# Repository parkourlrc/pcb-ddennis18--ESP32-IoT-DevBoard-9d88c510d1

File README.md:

# ESP32-IoT PCB

An ESP32-C3 based IoT controller board designed in KiCad. The board combines
wireless control, sensor interfaces, local storage, audio/light sensing, USB
connectivity, and single-cell Li-ion battery support on a compact four-layer
PCB.

## Main features

- **ESP32-C3-WROOM-02-H4** wireless microcontroller module
- **BME280** environmental sensor
- **MicroSD card** interface
- **W25Q32JV** external SPI flash
- **MAX4466** microphone amplifier and **CMC-5042PF-AC** microphone
- **TEMT6000X01** ambient light sensor
- **USB-C** connector with:
  - CP2102N USB-to-UART bridge
  - USB ESD protection
  - Boot and reset controls
- **Single-cell Li-ion power path**:
  - MCP73871 charger/power-path controller
  - JST battery connector
  - 3.3 V LM1117 regulator
- Status and activity LEDs
- Exposed SPI test points for SCLK, MOSI, MISO, chip select, and SD chip select
- Two M2 mounting holes

## PCB specifications

| Property | Value |
| --- | --- |
| Board thickness | 1.6 mm |
| Layer count | 4 copper layers |
| Copper stack | F.Cu / In1.Cu / In2.Cu / B.Cu |
| Copper thickness | 35 µm per copper layer |
| Core material | FR-4 |
| Approximate outline | 96.5 mm × 54.4 mm |
| Minimum routed trace width | 0.20 mm |
| Minimum routed spacing | 0.15 mm |
| Solder mask | Top and bottom |
| Silkscreen | Top and bottom |
| Finish | Not specified in the KiCad board setup; confirm with the fabricator |

The board outline includes a stepped/notched section around the USB connector
edge. Use the `Edge.Cuts` layer in the KiCad board file, rather than the
approximate dimensions above, for fabrication.

## Repository layout

### Design files

- [`ESP32-IoT.kicad_pcb`](./ESP32-IoT.kicad_pcb) — PCB layout
- [`ESP32-IoT.kicad_sch`](./ESP32-IoT.kicad_sch) — main schematic
- [`esp32-c3-02.kicad_sch`](./esp32-c3-02.kicad_sch) — ESP32-C3 subsystem
- [`sensors.kicad_sch`](./sensors.kicad_sch) — sensor subsystem
- [`user-interface.kicad_sch`](./user-interface.kicad_sch) — user-interface subsystem
- [`ESP32-IoT.kicad_pro`](./ESP32-IoT.kicad_pro) — KiCad project

### Libraries and reference material

- [`Libraries/Footprints/`](./Libraries/Footprints/) — project-specific footprints
- [`Libraries/Symbols/`](./Libraries/Symbols/) — project-specific symbols
- [`Libraries/3D models/`](./Libraries/3D%20models/) — STEP models used by the board
- [`Datasheets/`](./Datasheets/) — component datasheets
- [`fp-lib-table`](./fp-lib-table) and [`sym-lib-table`](./sym-lib-table) — project library configuration

## Opening the design

1. Install KiCad with PCB Editor and Schematic Editor.
2. Clone or download this repository while preserving the directory layout.
3. Open [`ESP32-IoT.kicad_pro`](./ESP32-IoT.kicad_pro).
4. Open the schematic and PCB from the KiCad project manager.
5. Keep the project-local `Libraries` directory beside the project files so the
   paths in `fp-lib-table` and `sym-lib-table` resolve correctly.

The PCB was saved by KiCad 10.0. Older KiCad releases may not be able to open
the board without conversion. Save a copy before converting the project.

## Assembly and bring-up notes

Populate and inspect the power section before fitting the ESP32-C3 module.
Check for shorts between `+3.3V`, USB VBUS, battery input, and `GND`, then
verify the regulator output with a current-limited supply.

For first power-up:

1. Leave the battery disconnected and power the board from USB.
2. Verify the 3.3 V rail and the power/status LED.
3. Confirm that the CP2102N enumerates over USB.
4. Use the **BOOT** and **RESET** switches to enter the ESP32-C3 download
   mode.
5. Program and test the ESP32-C3 firmware before connecting a battery.

Observe the polarity markings for the battery connector and polarized
capacitors. Do not connect a Li-ion cell until the charger and power-path
voltages have been verified.

## Design status

This repository contains the KiCad source and exported fabrication files.
Firmware, a complete assembly BOM, and a documented connector pinout are not
included in the current project snapshot. Validate the latest schematic,
component values, ERC/DRC results, and manufacturer capabilities before
production.

## License

This project is licensed under the [MIT License](./LICENSE).

The MIT license allows reuse, modification, distribution, and commercial use,
provided that the copyright notice and permission notice are retained in all
copies or substantial portions of the project.

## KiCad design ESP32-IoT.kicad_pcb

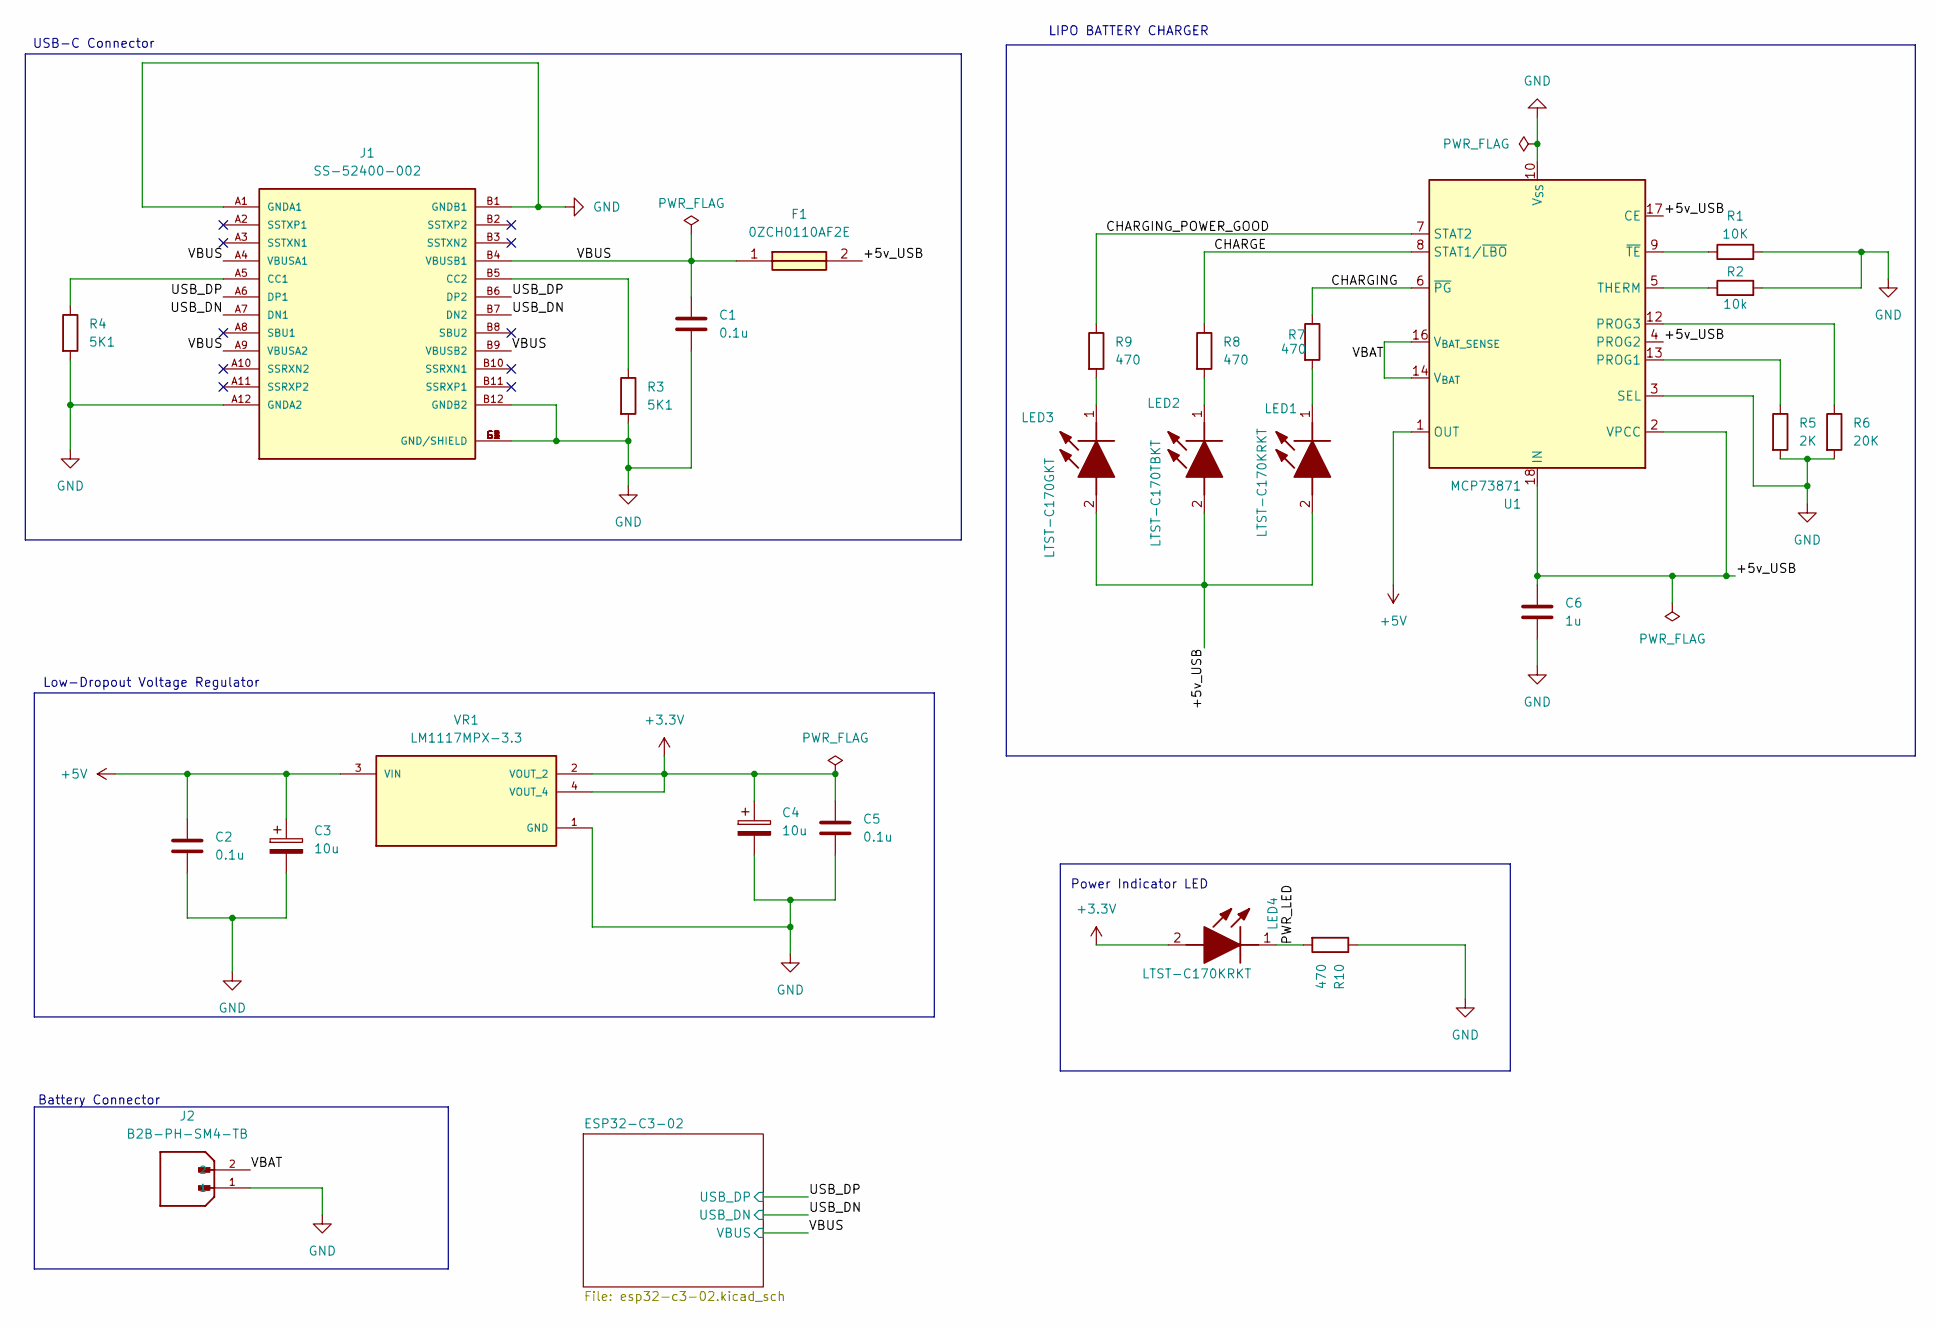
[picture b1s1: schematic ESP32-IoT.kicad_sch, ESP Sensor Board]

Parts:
C1, C2, C5: 0.1u; C_0805_2012Metric
C3, C4: 10u; T491A
C6: 1u; C_0805_2012Metric
F1: 0ZCH0110AF2E; FUSC3226X100N; Manufacturer_Part_Number 0ZCH0110AF2E
J1: SS-52400-002; BELFUSE_SS-52400-002; PARTREV A0
J2: B2B-PH-SM4-TB; JST_B2B-PH-SM4-TB; PARTREV N/A
LED1, LED4: LTST-C170KRKT; LEDC2012X120N; Manufacturer_Part_Number LTST-C170KRKT; Mouser Part Number 859-LTST-C170KRKT
LED2: LTST-C170TBKT; LEDC2012X120N; Manufacturer_Part_Number LTST-C170TBKT; Mouser Part Number 859-LTST-C170TBKT
LED3: LTST-C170GKT; LEDC2012X120N; Manufacturer_Part_Number LTST-C170GKT; Mouser Part Number 859-LTST-C170GKT
R1: 10K; R_0805_2012Metric
R2: 10k; R_0805_2012Metric
R3, R4: 5K1; R_0805_2012Metric
R5: 2K; R_0805_2012Metric
R6: 20K; R_0805_2012Metric
R7, R8, R9, R10: 470; R_0805_2012Metric
U1: MCP73871; QFN-20-1EP_4x4mm_P0.5mm_EP2.5x2.5mm
VR1: LM1117MPX-3.3; VREG_LM1117MPX-3.3

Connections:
+3.3V: C4.1, C5.1, LED4.2 (A), VR1.2 (VOUT_2), VR1.4 (VOUT_4); also elsewhere on the board
+5V: C2.1, C3.1, U1.1 (OUT), U1.20 (OUT), VR1.3 (VIN)
/+5v_USB: C6.1, F1.2, LED1.2 (A), LED2.2 (A), LED3.2 (A), U1.2 (VPCC), U1.4 (PROG2), U1.17 (CE), U1.18 (IN), U1.19 (IN)
/CHARGE: R8.1, U1.8 (STAT1/~LBO)
/CHARGING: R7.1, U1.6 (~PG)
/CHARGING_POWER_GOOD: R9.1, U1.7 (STAT2)
/PWR_LED: LED4.1 (K), R10.2; also elsewhere on the board
/USB_DN: J1.A7 (DN1), J1.B7 (DN2); also elsewhere on the board
/USB_DP: J1.A6 (DP1), J1.B6 (DP2); also elsewhere on the board
/VBAT: J2.2, U1.14 (V_{BAT}), U1.15 (V_{BAT}), U1.16 (V_{BAT_SENSE})
/VBUS: C1.1, F1.1, J1.A4 (VBUSA1), J1.A9 (VBUSA2), J1.B4 (VBUSB1), J1.B9 (VBUSB2); also elsewhere on the board
GND: C1.2, C2.2, C3.2, C4.2, C5.2, C6.2, J1.A1 (GNDA1), J1.A12 (GNDA2), J1.B1 (GNDB1), J1.B12 (GNDB2), J1.G1 (GND/SHIELD), J1.G2 (GND/SHIELD), J1.G3 (GND/SHIELD), J1.G4 (GND/SHIELD), J1.S1 (GND/SHIELD), J1.S2 (GND/SHIELD), J1.S3 (GND/SHIELD), J1.S4 (GND/SHIELD), J2.1, R1.2, R2.2, R3.2, R4.2, R5.2, R6.2, R10.1, U1.3 (SEL), U1.10 (V_{SS}), U1.11 (V_{SS}), U1.21 (V_{SS}), VR1.1 (GND); also elsewhere on the board
unnamed: J1.A5 (CC1), R4.1
unnamed: J1.B5 (CC2), R3.1
unnamed: LED1.1 (K), R7.2
unnamed: LED2.1 (K), R8.2
unnamed: LED3.1 (K), R9.2
unnamed: R5.1, U1.13 (PROG1)
unnamed: R6.1, U1.12 (PROG3)
unnamed: R2.1, U1.5 (THERM)
unnamed: R1.1, U1.9 (~TE)

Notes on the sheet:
Battery Connector
Low-Dropout Voltage Regulator
USB-C Connector
LIPO BATTERY CHARGER
Power Indicator LED

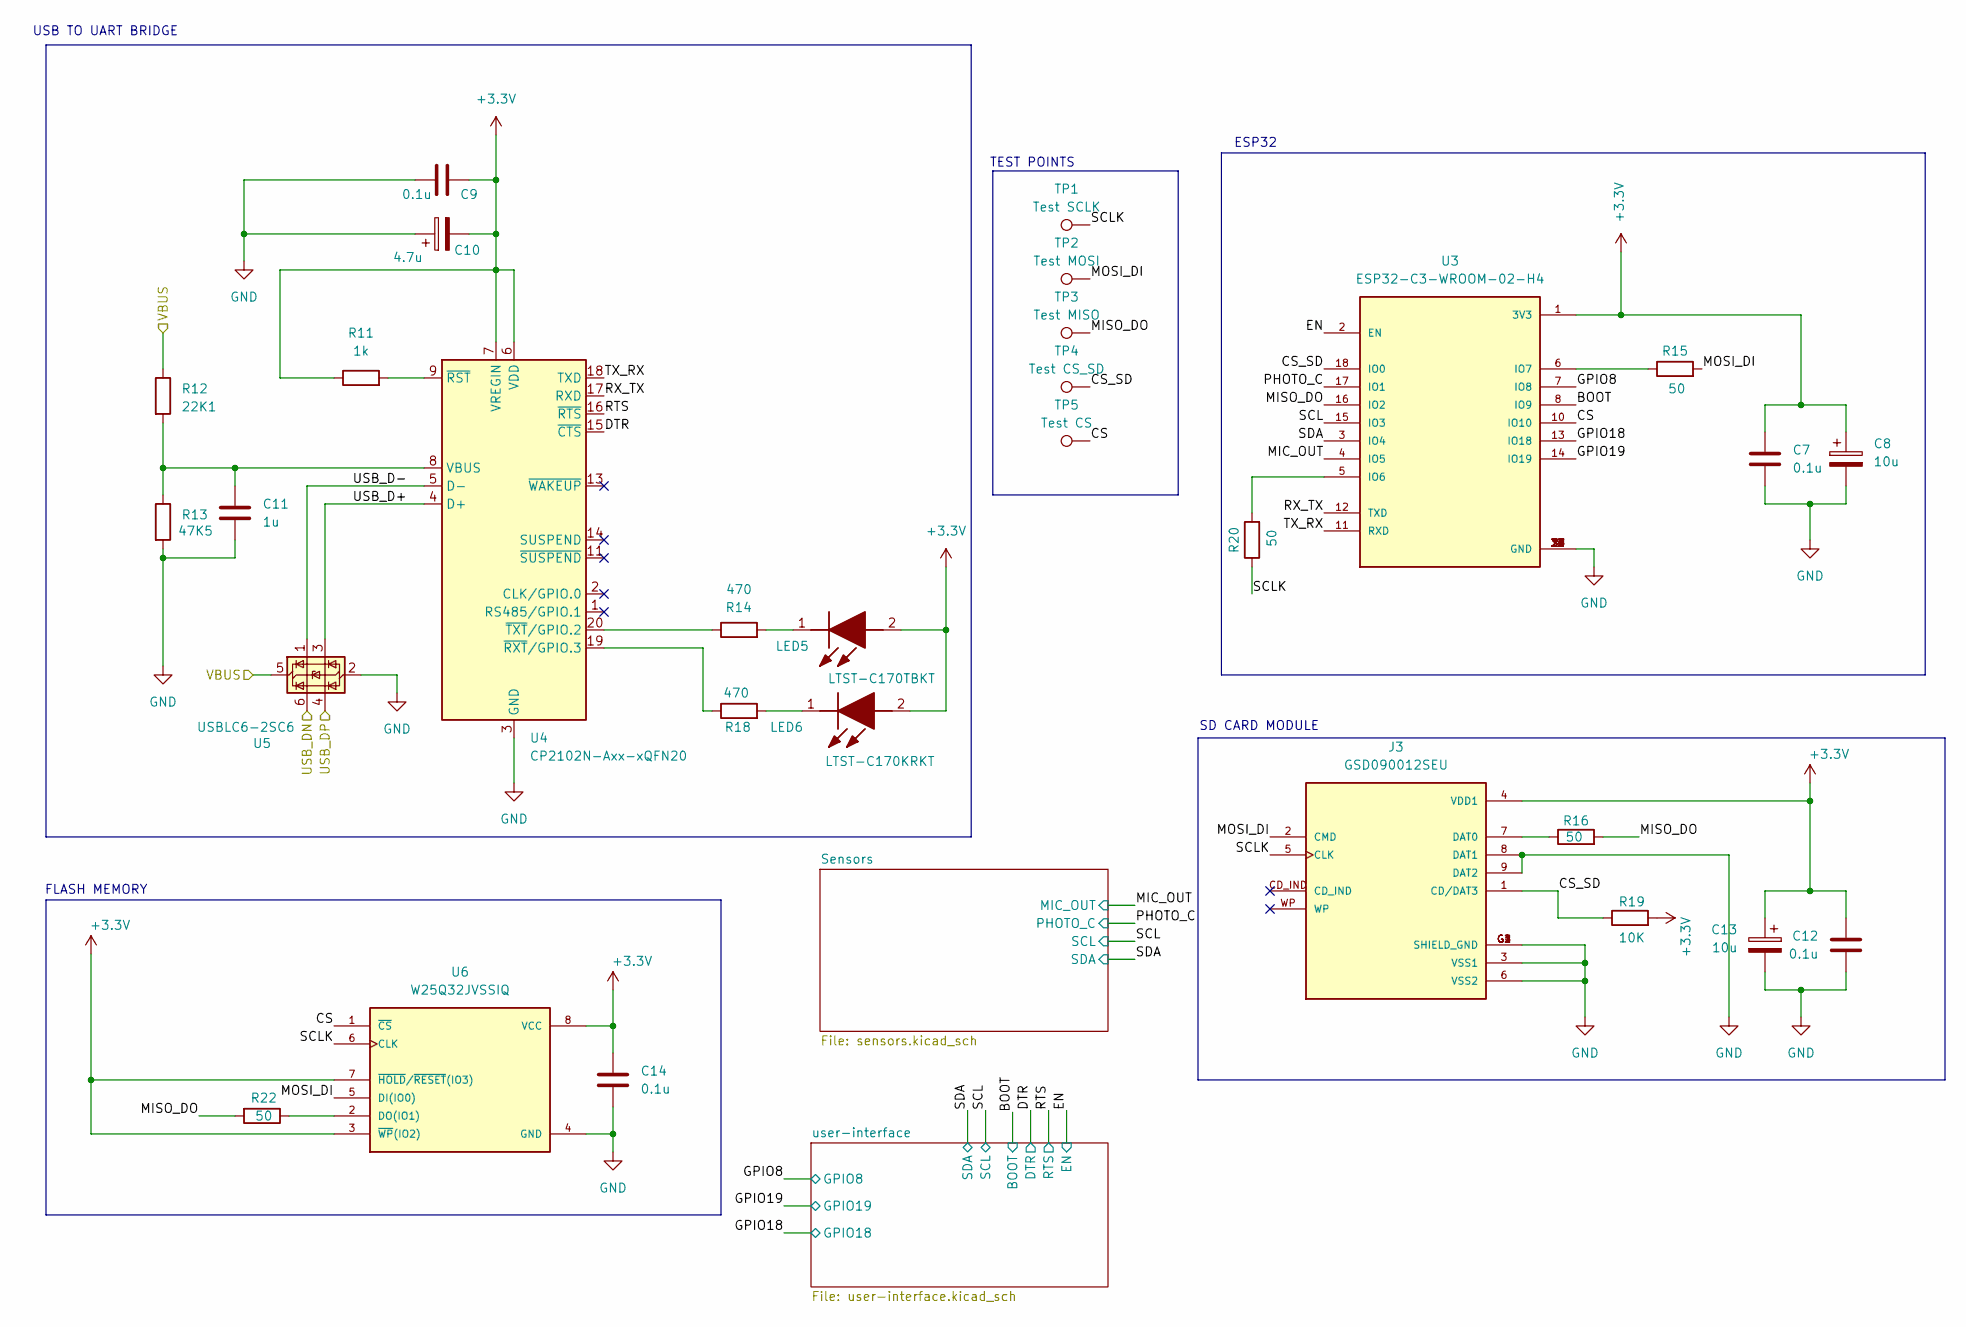
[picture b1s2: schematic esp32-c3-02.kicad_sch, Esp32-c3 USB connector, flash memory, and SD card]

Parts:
C7, C9, C12, C14: 0.1u; C_0805_2012Metric
C8, C13: 10u; T491A
C10: 4.7u; T491A
C11: 1u; C_0805_2012Metric
J3: GSD090012SEU; AMPHENOL_GSD090012SEU; PARTREV E
LED5: LTST-C170TBKT; LEDC2012X120N; Manufacturer_Part_Number LTST-C170TBKT; Mouser Part Number 859-LTST-C170TBKT
LED6: LTST-C170KRKT; LEDC2012X120N; Manufacturer_Part_Number LTST-C170KRKT; Mouser Part Number 859-LTST-C170KRKT
R11: 1k; R_0805_2012Metric
R12: 22K1; R_0805_2012Metric
R13: 47K5; R_0805_2012Metric
R14, R18: 470; R_0805_2012Metric
R15, R16, R20, R22: 50; R_0805_2012Metric
R19: 10K; R_0805_2012Metric
TP1: Test SCLK; TestPoint_Pad_D1.0mm
TP2: Test MOSI; TestPoint_Pad_D1.0mm
TP3: Test MISO; TestPoint_Pad_D1.0mm
TP4: Test CS_SD; TestPoint_Pad_D1.0mm
TP5: Test CS; TestPoint_Pad_D1.0mm
U3: ESP32-C3-WROOM-02-H4; MODULE_ESP32-C3-WROOM-02-H4
U4: CP2102N-Axx-xQFN20; SiliconLabs_QFN-20-1EP_3x3mm_P0.5mm_EP1.8x1.8mm
U5: USBLC6-2SC6; SOT-23-6
U6: W25Q32JVSSIQ; SOIC127P790X216-8N; M_PART_NUMBER W25QXX

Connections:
+3.3V: C7.1, C8.1, C9.2, C10.2, C12.1, C13.1, C14.1, J3.4 (VDD1), LED5.2 (A), LED6.2 (A), R11.1, R19.2, U3.1 (3V3), U4.6 (VDD), U4.7 (VREGIN), U6.3 (~WP(IO2)), U6.7 (~HOLD/~RESET(IO3)), U6.8 (VCC); also elsewhere on the board
/ESP32-C3-02/BOOT: U3.8 (IO9); also elsewhere on the board
/ESP32-C3-02/CS: TP5.1 (1_1), U3.10 (IO10), U6.1 (~CS)
/ESP32-C3-02/CS_SD: J3.1 (CD/DAT3), R19.1, TP4.1 (1_1), U3.18 (IO0)
/ESP32-C3-02/DTR: U4.15 (~CTS); also elsewhere on the board
/ESP32-C3-02/EN: U3.2 (EN); also elsewhere on the board
/ESP32-C3-02/GPIO8: U3.7 (IO8); also elsewhere on the board
/ESP32-C3-02/GPIO18: U3.13 (IO18); also elsewhere on the board
/ESP32-C3-02/GPIO19: U3.14 (IO19); also elsewhere on the board
/ESP32-C3-02/MIC_OUT: U3.4 (IO5); also elsewhere on the board
/ESP32-C3-02/MISO_DO: R16.2, R22.2, TP3.1 (1_1), U3.16 (IO2)
/ESP32-C3-02/MOSI_DI: J3.2 (CMD), R15.2, TP2.1 (1_1), U6.5 (DI(IO0))
/ESP32-C3-02/PHOTO_C: U3.17 (IO1); also elsewhere on the board
/ESP32-C3-02/RTS: U4.16 (~RTS); also elsewhere on the board
/ESP32-C3-02/RX_TX: U3.12 (TXD), U4.17 (RXD)
/ESP32-C3-02/SCL: U3.15 (IO3); also elsewhere on the board
/ESP32-C3-02/SCLK: J3.5 (CLK), R20.1, TP1.1 (1_1), U6.6 (CLK)
/ESP32-C3-02/SDA: U3.3 (IO4); also elsewhere on the board
/ESP32-C3-02/TX_RX: U3.11 (RXD), U4.18 (TXD)
/ESP32-C3-02/USB_D+: U4.4 (D+), U5.3 (I/O2)
/ESP32-C3-02/USB_D-: U4.5 (D-), U5.1 (I/O1)
/USB_DN: U5.6 (I/O1); also elsewhere on the board
/USB_DP: U5.4 (I/O2); also elsewhere on the board
/VBUS: R12.1, U5.5 (VBUS); also elsewhere on the board
GND: C7.2, C8.2, C9.1, C10.1, C11.2, C12.2, C13.2, C14.2, J3.3 (VSS1), J3.6 (VSS2), J3.8 (DAT1), J3.9 (DAT2), J3.G1 (SHIELD_GND), J3.G2 (SHIELD_GND), J3.G3 (SHIELD_GND), J3.G4 (SHIELD_GND), R13.2, U3.9 (GND), U3.19 (GND), U3.20 (GND), U3.21 (GND), U3.22 (GND), U3.23 (GND), U3.24 (GND), U3.25 (GND), U3.26 (GND), U3.27 (GND), U3.28 (GND), U3.29 (GND), U3.30 (GND), U3.31 (GND), U3.32 (GND), U3.33 (GND), U3.34 (GND), U3.35 (GND), U3.36 (GND), U3.37 (GND), U3.38 (GND), U3.39 (GND), U4.3 (GND), U4.12 (GND), U4.21 (GND), U5.2 (GND), U6.4 (GND); also elsewhere on the board
unnamed: J3.7 (DAT0), R16.1
unnamed: LED5.1 (K), R14.2
unnamed: LED6.1 (K), R18.2
unnamed: R20.2, U3.5 (IO6)
unnamed: R15.1, U3.6 (IO7)
unnamed: C11.1, R12.2, R13.1, U4.8 (VBUS)
unnamed: R11.2, U4.9 (~RST)
unnamed: R18.1, U4.19 (~RXT/GPIO.3)
unnamed: R14.1, U4.20 (~TXT/GPIO.2)
unnamed: R22.1, U6.2 (DO(IO1))

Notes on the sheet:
TEST POINTS
USB TO UART BRIDGE
FLASH MEMORY
ESP32
SD CARD MODULE

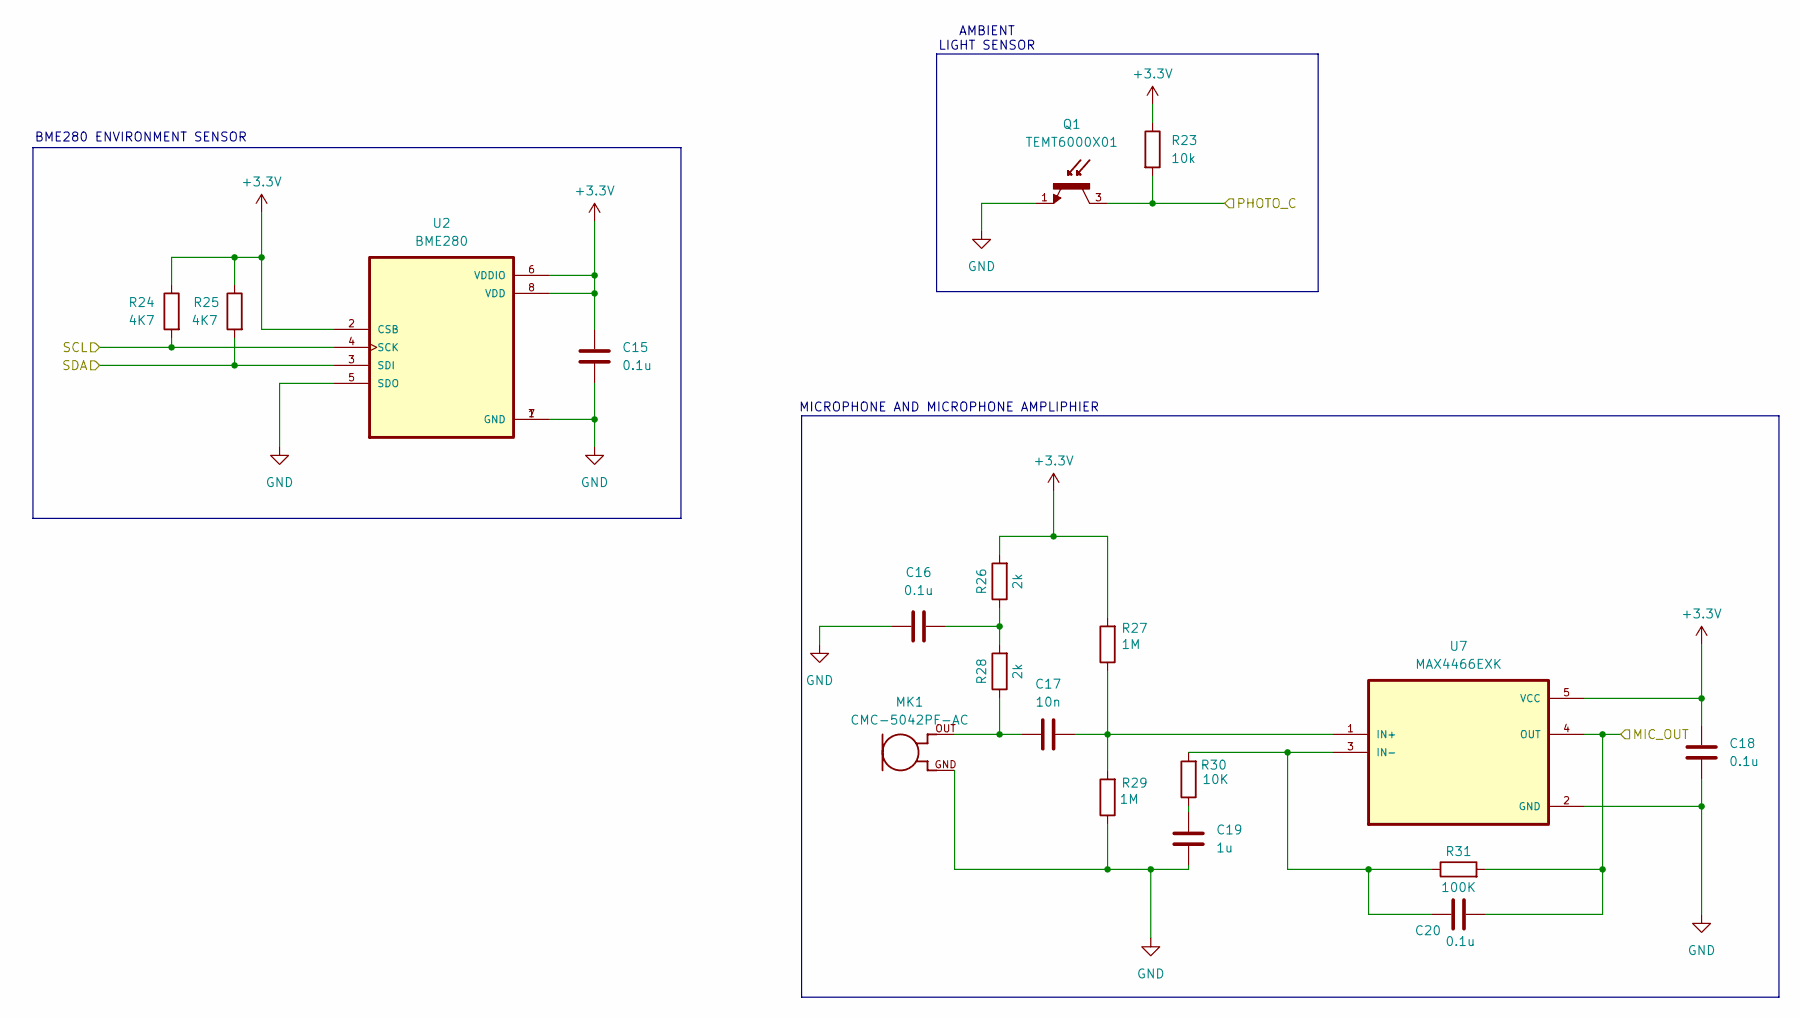
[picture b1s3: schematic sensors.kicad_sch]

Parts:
C15, C16, C18, C20: 0.1u; C_0805_2012Metric
C17: 10n; C_0805_2012Metric
C19: 1u; C_0805_2012Metric
MK1: CMC-5042PF-AC; CUI_CMC-5042PF-AC
Q1: TEMT6000X01; TRANS_TEMT6000X01; PARTREV 1.9
R23: 10k; R_0805_2012Metric
R24, R25: 4K7; R_0805_2012Metric
R26, R28: 2k; R_0805_2012Metric
R27, R29: 1M; R_0805_2012Metric
R30: 10K; R_0805_2012Metric
R31: 100K; R_0805_2012Metric
U2: BME280; PSON65P250X250X100-8N
U7: MAX4466EXK; SOT65P210X110-5N

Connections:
+3.3V: C15.1, C18.1, R23.1, R24.1, R25.1, R26.2, R27.2, U2.2 (CSB), U2.6 (VDDIO), U2.8 (VDD), U7.5 (VCC); also elsewhere on the board
/ESP32-C3-02/MIC_OUT: C20.2, R31.2, U7.4 (OUT); also elsewhere on the board
/ESP32-C3-02/PHOTO_C: Q1.3, R23.2; also elsewhere on the board
/ESP32-C3-02/SCL: R24.2, U2.4 (SCK); also elsewhere on the board
/ESP32-C3-02/SDA: R25.2, U2.3 (SDI); also elsewhere on the board
GND: C15.2, C16.1, C18.2, C19.2, MK1.GND, Q1.1, R29.1, U2.1 (GND), U2.5 (SDO), U2.7 (GND), U7.2 (GND); also elsewhere on the board
unnamed: C16.2, R26.1, R28.2
unnamed: C17.1, MK1.OUT, R28.1
unnamed: C19.1, R30.1
unnamed: C17.2, R27.1, R29.2, U7.1 (IN+)
unnamed: C20.1, R30.2, R31.1, U7.3 (IN-)

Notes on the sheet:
MICROPHONE AND MICROPHONE AMPLIPHIER
AMBIENT LIGHT SENSOR
BME280 ENVIRONMENT SENSOR

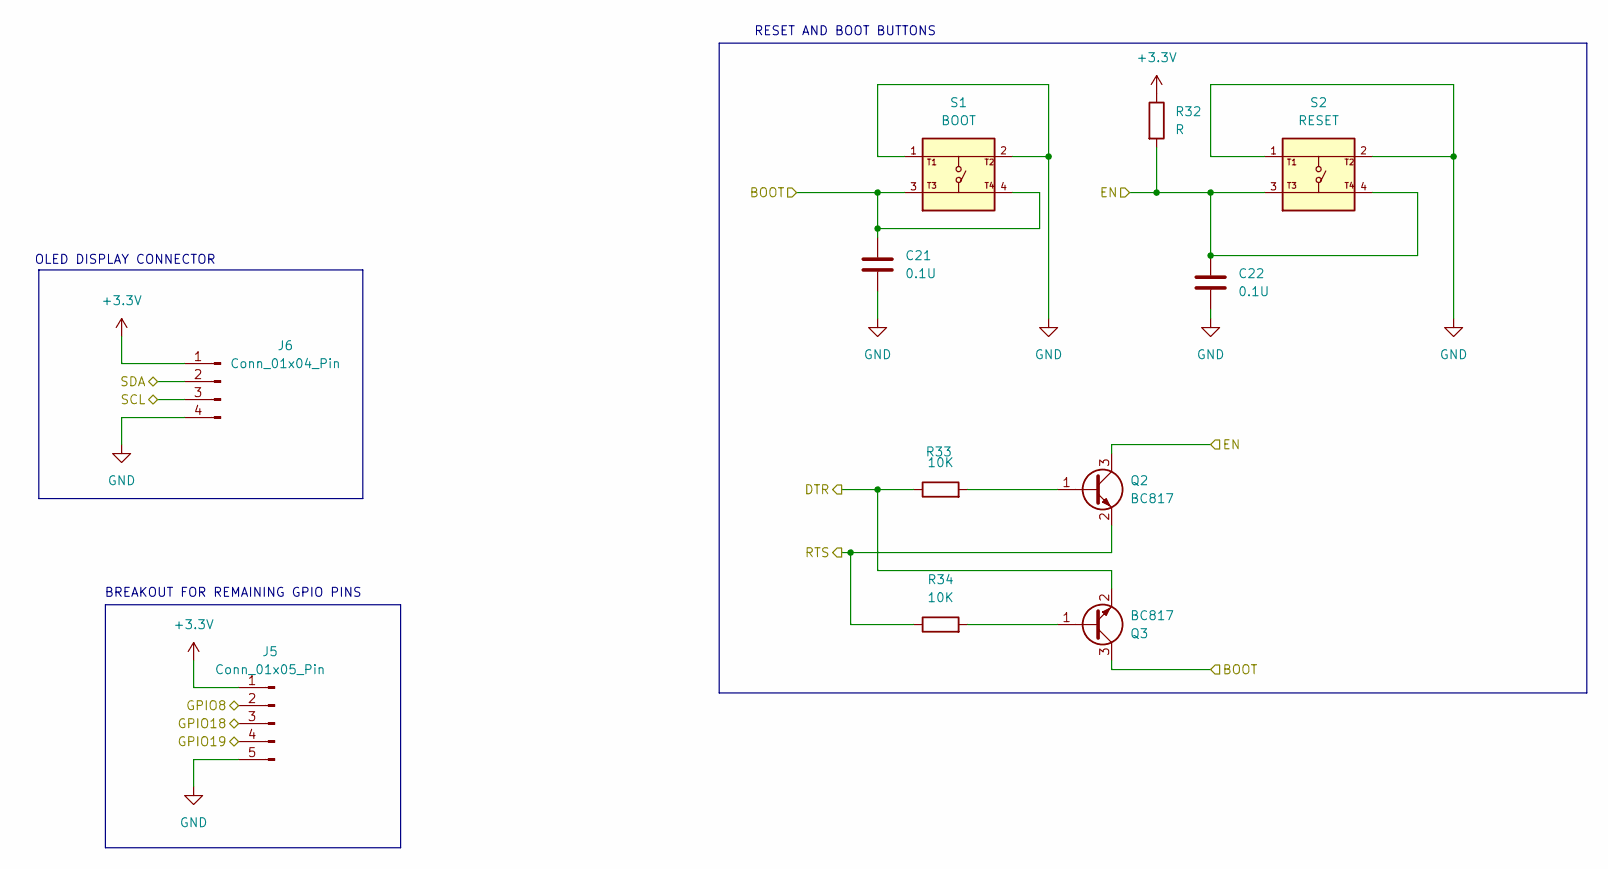
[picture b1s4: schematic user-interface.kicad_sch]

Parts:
C21, C22: 0.1U; C_0805_2012Metric
J5: Conn_01x05_Pin; PinHeader_1x05_P2.54mm_Vertical
J6: Conn_01x04_Pin; PinHeader_1x04_P2.54mm_Vertical
Q2, Q3: BC817; SOT-23
R32: R; R_0805_2012Metric
R33, R34: 10K; R_0805_2012Metric
S1: BOOT; SW_USLPT2819DT2TR; PARTREV P
S2: RESET; SW_USLPT2819DT2TR; PARTREV P

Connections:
+3.3V: J5.1, J6.1, R32.1; also elsewhere on the board
/ESP32-C3-02/BOOT: C21.1, Q3.3 (C), S1.3, S1.4; also elsewhere on the board
/ESP32-C3-02/DTR: Q3.2 (E), R33.1; also elsewhere on the board
/ESP32-C3-02/EN: C22.1, Q2.3 (C), R32.2, S2.3, S2.4; also elsewhere on the board
/ESP32-C3-02/GPIO8: J5.2; also elsewhere on the board
/ESP32-C3-02/GPIO18: J5.3; also elsewhere on the board
/ESP32-C3-02/GPIO19: J5.4; also elsewhere on the board
/ESP32-C3-02/RTS: Q2.2 (E), R34.1; also elsewhere on the board
/ESP32-C3-02/SCL: J6.3; also elsewhere on the board
/ESP32-C3-02/SDA: J6.2; also elsewhere on the board
GND: C21.2, C22.2, J5.5, J6.4, S1.1, S1.2, S2.1, S2.2; also elsewhere on the board
unnamed: Q2.1 (B), R33.2
unnamed: Q3.1 (B), R34.2

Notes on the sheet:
OLED DISPLAY CONNECTOR
BREAKOUT FOR REMAINING GPIO PINS
RESET AND BOOT BUTTONS

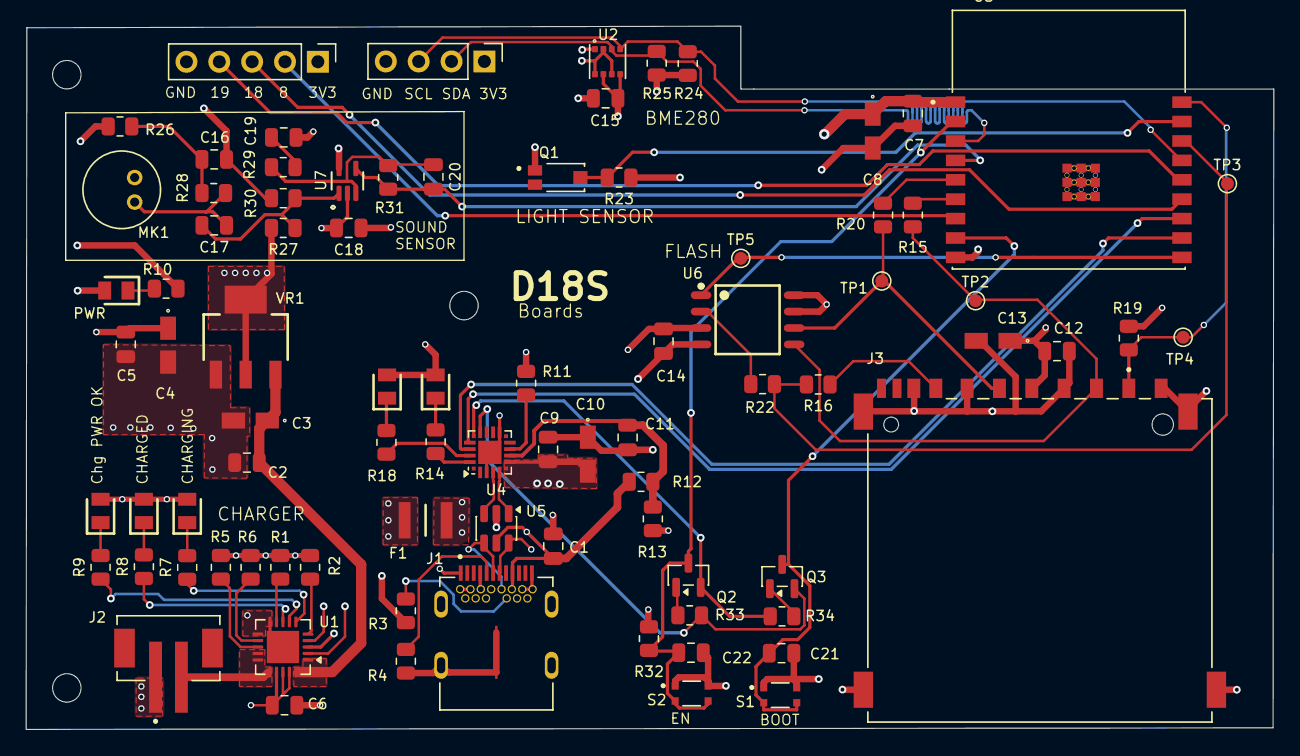
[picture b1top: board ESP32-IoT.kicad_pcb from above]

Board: 4 copper layers, 96.5 x 54.4 mm, 85 parts (0 on the bottom side), 58 nets.

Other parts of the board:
PWR: LTST-C170KRKT; LEDC2012X120N

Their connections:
+3.3V: PWR.2 (A); also elsewhere on the board
/PWR_LED: PWR.1 (K); also elsewhere on the board
